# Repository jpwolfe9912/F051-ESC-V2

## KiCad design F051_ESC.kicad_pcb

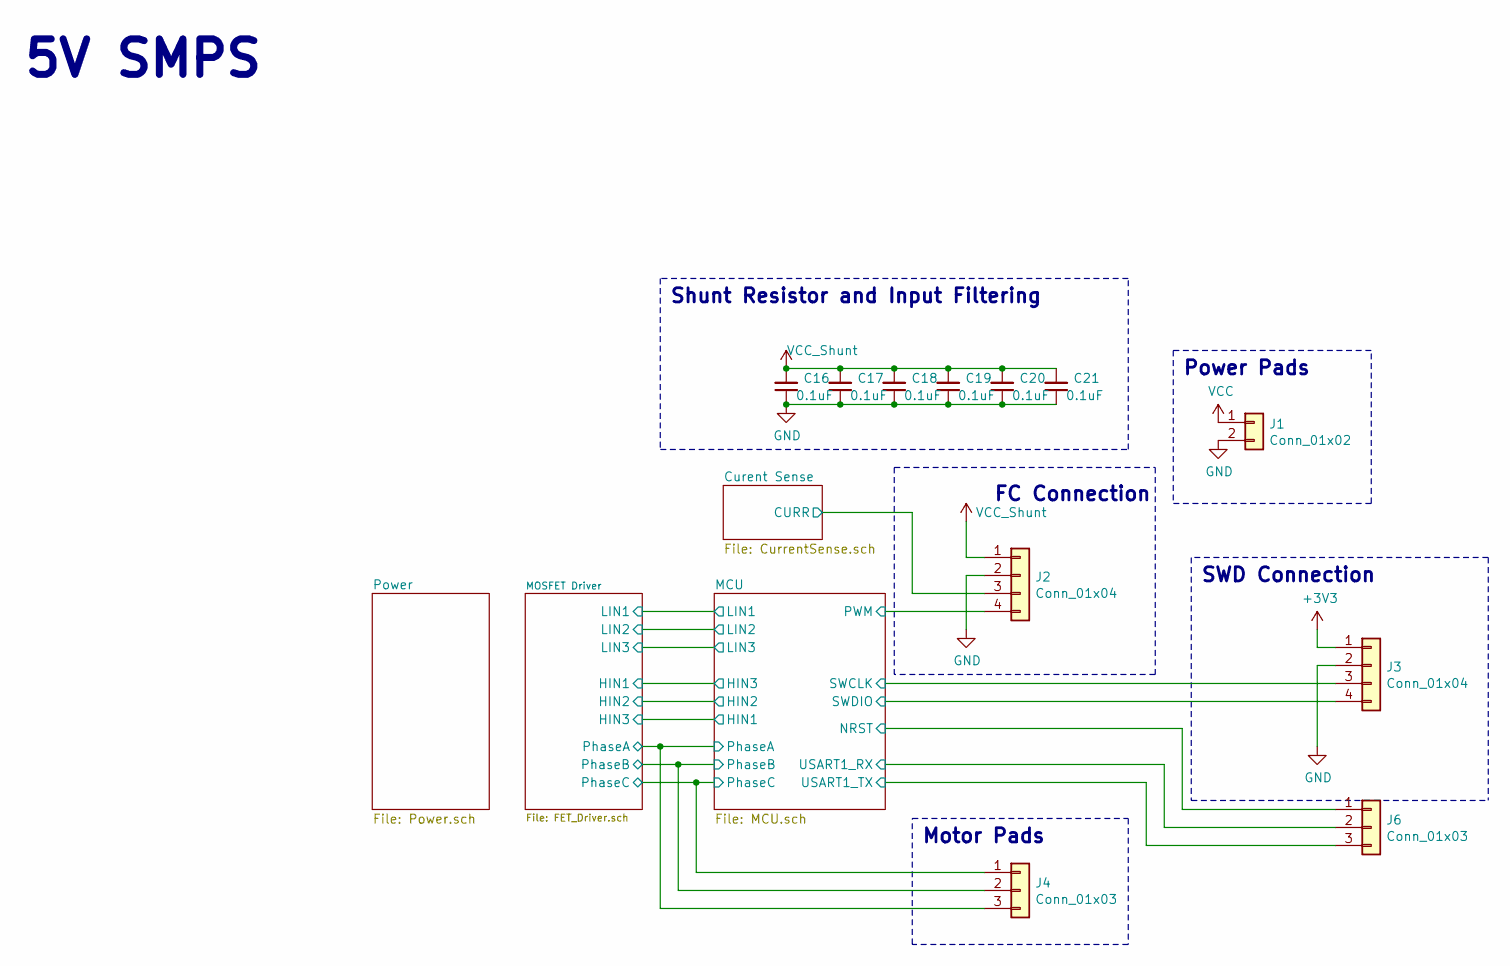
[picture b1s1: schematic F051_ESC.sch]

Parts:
C16, C17, C18, C19, C20, C21: 0.1uF; C_1206_3216Metric
J1: Conn_01x02; Conn_PowerPad
J2: Conn_01x04; JST_SH_SM04B-SRSS-TB_1x04-1MP_P1.00mm_Horizontal
J3: Conn_01x04; PinHeader_1x04_P2.54mm_Vertical
J4: Conn_01x03; Conn_MotorPhase
J6: Conn_01x03; PinHeader_1x03_P2.54mm_Vertical

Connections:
+3V3: J3.1; also elsewhere on the board
/Curent Sense/CURR: J2.3; also elsewhere on the board
/MCU/NRST: J6.1; also elsewhere on the board
/MCU/PWM: J2.4; also elsewhere on the board
/MCU/PhaseA: J4.3; also elsewhere on the board
/MCU/PhaseB: J4.2; also elsewhere on the board
/MCU/PhaseC: J4.1; also elsewhere on the board
/MCU/SWCLK: J3.3; also elsewhere on the board
/MCU/SWDIO: J3.4; also elsewhere on the board
/MCU/USART1_RX: J6.2; also elsewhere on the board
/MCU/USART1_TX: J6.3; also elsewhere on the board
GND: C16.1, C17.1, C18.1, C19.1, C20.1, C21.1, J1.2, J2.2, J3.2; also elsewhere on the board
VCC: J1.1; also elsewhere on the board
VCC_Shunt: C16.2, C17.2, C18.2, C19.2, C20.2, C21.2, J2.1; also elsewhere on the board

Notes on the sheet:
5V SMPS
SWD Connection
FC Connection
Motor Pads
Shunt Resistor and Input Filtering
Power Pads

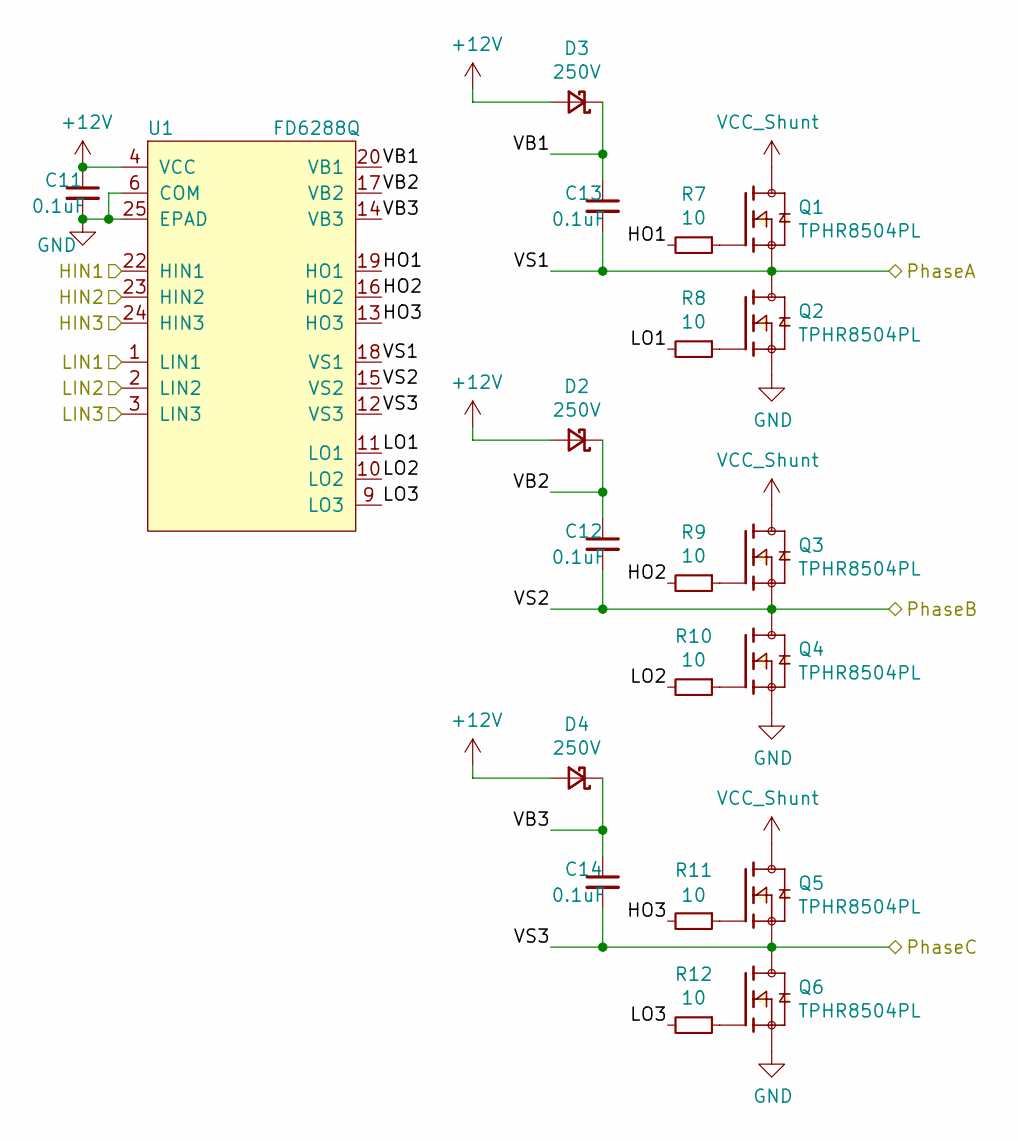
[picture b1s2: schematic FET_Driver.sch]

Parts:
C11: 0.1uF; C_0402_1005Metric
C12, C13, C14: 0.1uF; C_0603_1608Metric
D2, D3, D4: 250V; D_SOD-523
Q1, Q2, Q3, Q4, Q5, Q6: TPHR8504PL; PARTREV 3
R7, R8, R9, R10, R11, R12: 10; R_0402_1005Metric
U1: FD6288Q; QFN-24-1EP_4x4mm_P0.5mm_EP2.7x2.7mm

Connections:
+12V: C11.1, D2.2 (A), D3.2 (A), D4.2 (A), U1.4 (VCC); also elsewhere on the board
/MCU/HIN1: U1.24 (HIN3); also elsewhere on the board
/MCU/HIN2: U1.23 (HIN2); also elsewhere on the board
/MCU/LIN1: U1.1 (LIN1); also elsewhere on the board
/MCU/LIN2: U1.2 (LIN2); also elsewhere on the board
/MCU/LIN3: U1.3 (LIN3); also elsewhere on the board
/MCU/PhaseA: C13.2, Q1.1, Q1.2, Q1.3, Q2.5, Q2.6, Q2.7, Q2.8, Q2.9, U1.18 (VS1); also elsewhere on the board
/MCU/PhaseB: C12.2, Q3.1, Q3.2, Q3.3, Q4.5, Q4.6, Q4.7, Q4.8, Q4.9, U1.15 (VS2); also elsewhere on the board
/MCU/PhaseC: C14.2, Q5.1, Q5.2, Q5.3, Q6.5, Q6.6, Q6.7, Q6.8, Q6.9, U1.12 (VS3); also elsewhere on the board
/MOSFET Driver/HIN1: U1.22 (HIN1); also elsewhere on the board
/MOSFET Driver/HO1: R7.2, U1.19 (HO1)
/MOSFET Driver/HO2: R9.2, U1.16 (HO2)
/MOSFET Driver/HO3: R11.2, U1.13 (HO3)
/MOSFET Driver/LO1: R8.2, U1.11 (LO1)
/MOSFET Driver/LO2: R10.2, U1.10 (LO2)
/MOSFET Driver/LO3: R12.2, U1.9 (LO3)
/MOSFET Driver/VB1: C13.1, D3.1 (K), U1.20 (VB1)
/MOSFET Driver/VB2: C12.1, D2.1 (K), U1.17 (VB2)
/MOSFET Driver/VB3: C14.1, D4.1 (K), U1.14 (VB3)
GND: C11.2, Q2.1, Q2.2, Q2.3, Q4.1, Q4.2, Q4.3, Q6.1, Q6.2, Q6.3, U1.6 (COM), U1.25 (EPAD); also elsewhere on the board
unnamed: Q1.4, R7.1
unnamed: Q2.4, R8.1
unnamed: Q3.4, R9.1
unnamed: Q4.4, R10.1
unnamed: Q5.4, R11.1
unnamed: Q6.4, R12.1
VCC_Shunt: Q1.5, Q1.6, Q1.7, Q1.8, Q1.9, Q3.5, Q3.6, Q3.7, Q3.8, Q3.9, Q5.5, Q5.6, Q5.7, Q5.8, Q5.9; also elsewhere on the board

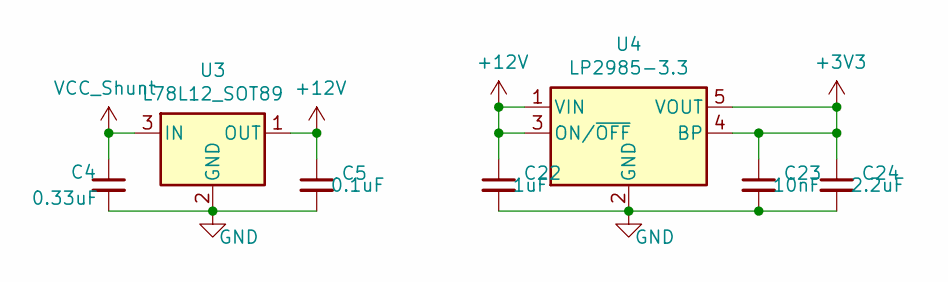
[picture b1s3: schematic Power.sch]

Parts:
C4: 0.33uF; C_0603_1608Metric
C5: 0.1uF; C_0603_1608Metric
C22: 1uF; C_0603_1608Metric
C23: 10nF; C_0402_1005Metric
C24: 2.2uF; C_0603_1608Metric
U3: L78L12_SOT89; SOT-89-3
U4: LP2985-3.3; SOT-23-5

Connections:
+3V3: C23.1, C24.1, U4.4 (BP), U4.5 (VOUT); also elsewhere on the board
+12V: C5.1, C22.1, U3.1 (OUT), U4.1 (VIN), U4.3 (ON/~OFF~); also elsewhere on the board
GND: C4.2, C5.2, C22.2, C23.2, C24.2, U3.2 (GND), U4.2 (GND); also elsewhere on the board
VCC_Shunt: C4.1, U3.3 (IN); also elsewhere on the board

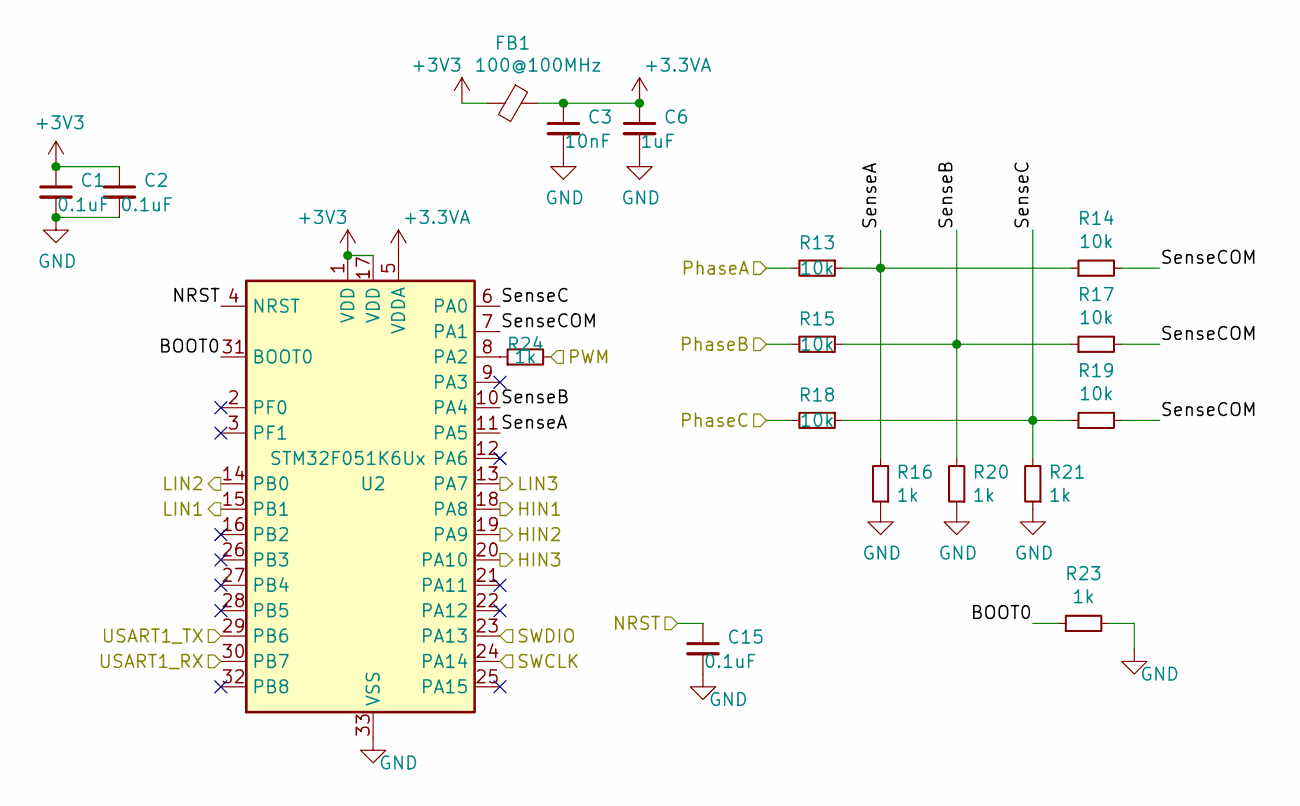
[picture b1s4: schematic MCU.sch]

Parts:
C1, C2, C15: 0.1uF; C_0402_1005Metric
C3: 10nF; C_0402_1005Metric
C6: 1uF; C_0402_1005Metric
FB1: 100@100MHz; L_0603_1608Metric
R13, R14, R15, R17, R18, R19: 10k; R_0402_1005Metric
R16, R20, R21, R23, R24: 1k; R_0402_1005Metric
U2: STM32F051K6Ux; QFN-32-1EP_5x5mm_P0.5mm_EP3.45x3.45mm

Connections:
+3.3VA: C3.1, C6.1, FB1.1, U2.5 (VDDA)
+3V3: C1.1, C2.1, FB1.2, U2.1 (VDD), U2.17 (VDD); also elsewhere on the board
/MCU/BOOT0: R23.1, U2.31 (BOOT0)
/MCU/HIN1: U2.18 (PA8); also elsewhere on the board
/MCU/HIN2: U2.19 (PA9); also elsewhere on the board
/MCU/LIN1: U2.15 (PB1); also elsewhere on the board
/MCU/LIN2: U2.14 (PB0); also elsewhere on the board
/MCU/LIN3: U2.13 (PA7); also elsewhere on the board
/MCU/NRST: C15.1, U2.4 (NRST); also elsewhere on the board
/MCU/PWM: R24.2; also elsewhere on the board
/MCU/PhaseA: R13.2; also elsewhere on the board
/MCU/PhaseB: R15.2; also elsewhere on the board
/MCU/PhaseC: R18.2; also elsewhere on the board
/MCU/SWCLK: U2.24 (PA14); also elsewhere on the board
/MCU/SWDIO: U2.23 (PA13); also elsewhere on the board
/MCU/SenseA: R13.1, R14.1, R16.2, U2.11 (PA5)
/MCU/SenseB: R15.1, R17.1, R20.2, U2.10 (PA4)
/MCU/SenseC: R18.1, R19.1, R21.2, U2.6 (PA0)
/MCU/SenseCOM: R14.2, R17.2, R19.2, U2.7 (PA1)
/MCU/USART1_RX: U2.30 (PB7); also elsewhere on the board
/MCU/USART1_TX: U2.29 (PB6); also elsewhere on the board
/MOSFET Driver/HIN1: U2.20 (PA10); also elsewhere on the board
GND: C1.2, C2.2, C3.2, C6.2, C15.2, R16.1, R20.1, R21.1, R23.2, U2.33 (VSS); also elsewhere on the board
unnamed: R24.1, U2.8 (PA2)

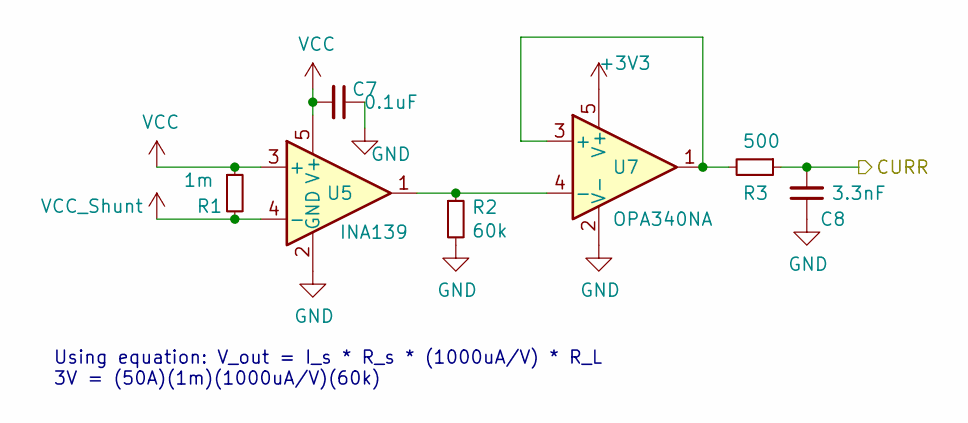
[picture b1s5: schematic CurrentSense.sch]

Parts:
C7: 0.1uF; C_0402_1005Metric
C8: 3.3nF; C_0402_1005Metric
R1: 1m; SCMM2512S5-R001F
R2: 60k; R_0402_1005Metric
R3: 500; R_0402_1005Metric
U5: INA139; SOT-23-5
U7: OPA340NA; SOT-23-5

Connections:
+3V3: U7.5 (V+); also elsewhere on the board
/Curent Sense/CURR: C8.2, R3.1; also elsewhere on the board
GND: C7.1, C8.1, R2.2, U5.2 (GND), U7.2 (V-); also elsewhere on the board
unnamed: R2.1, U5.1, U7.4 (-)
unnamed: R3.2, U7.1, U7.3 (+)
VCC: C7.2, R1.1, U5.3 (+), U5.5 (V+); also elsewhere on the board
VCC_Shunt: R1.2, U5.4 (-); also elsewhere on the board

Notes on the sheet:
Using equation: V_out = I_s * R_s * (1000uA/V) * R_L 3V = (50A)(1m)(1000uA/V)(60k)

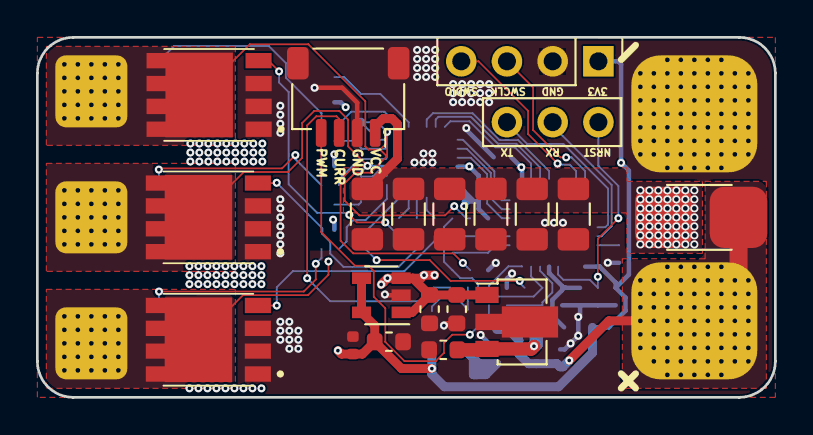
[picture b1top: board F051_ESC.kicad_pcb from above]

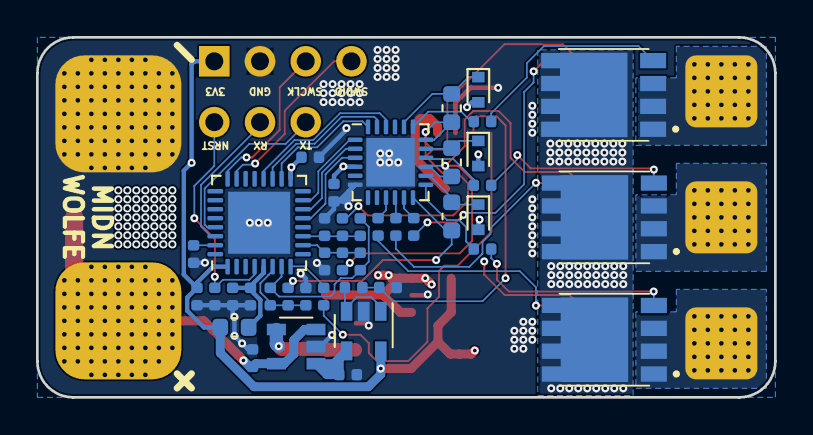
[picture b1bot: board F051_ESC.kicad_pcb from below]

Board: 4 copper layers, 41.0 x 20.0 mm, 63 parts (41 on the bottom side), 45 nets.

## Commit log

2021-03-15 New files
2021-03-16 Rerouting of a lot of layers
2021-03-16 Added vias and a little bit of rearranging
2021-03-16 Updated all PNGs
2021-03-16 deleted zip
2021-03-16 Moved via slightly
2021-03-16 On god, no clue what I changed on PCB. Added Gerbers though
